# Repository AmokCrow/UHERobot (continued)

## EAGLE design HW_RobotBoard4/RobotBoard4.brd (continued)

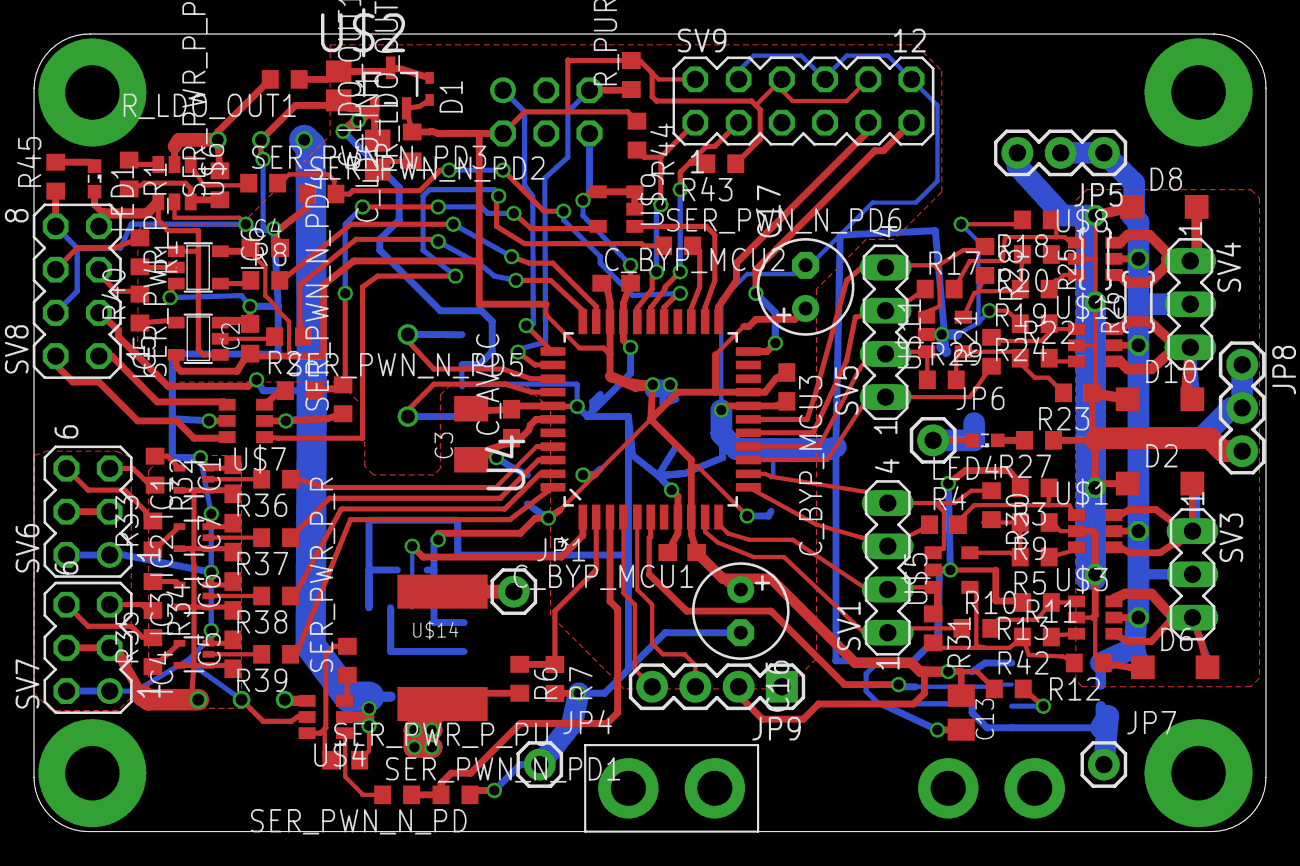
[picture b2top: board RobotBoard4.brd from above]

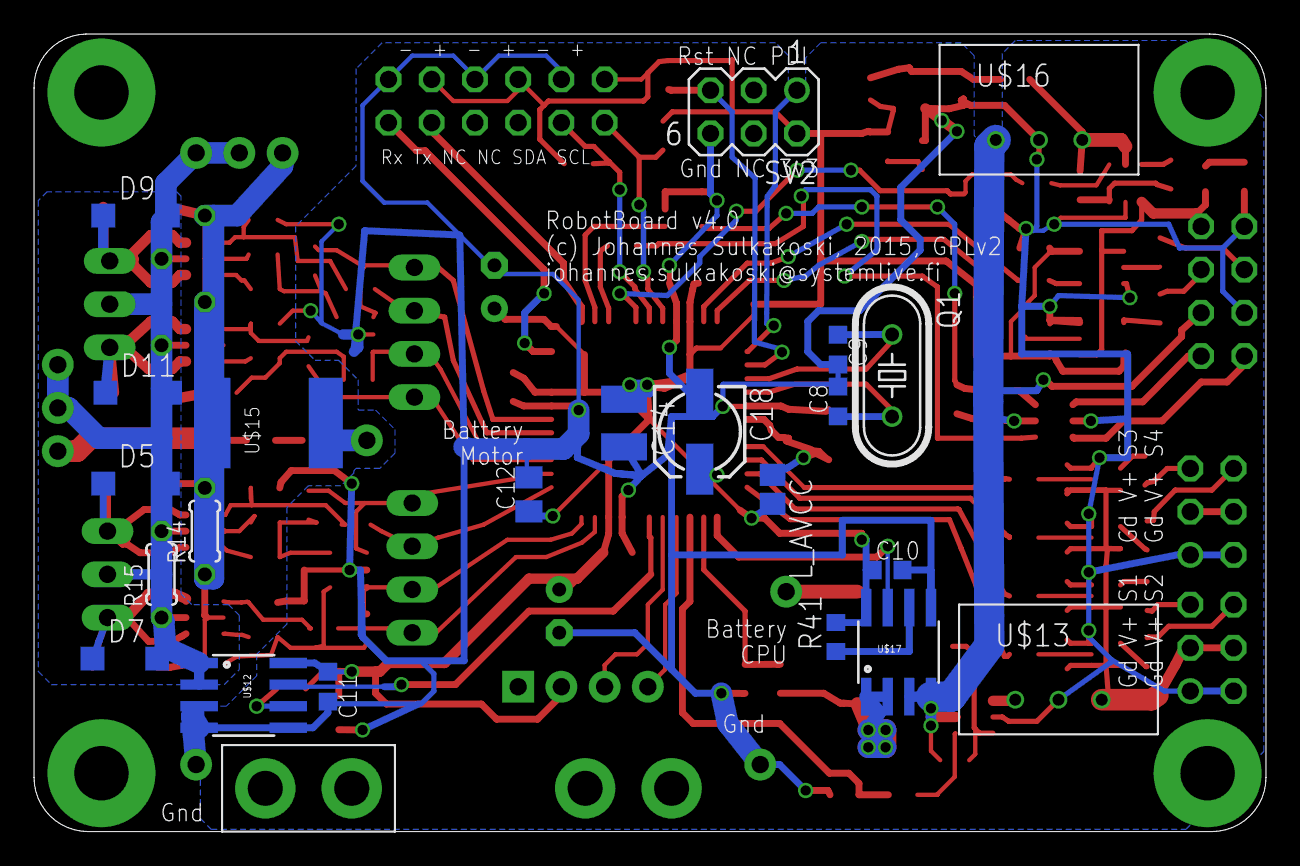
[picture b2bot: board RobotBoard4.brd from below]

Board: 4 copper layers, 72.4 x 46.9 mm, 140 parts (23 on the bottom side), 95 nets.

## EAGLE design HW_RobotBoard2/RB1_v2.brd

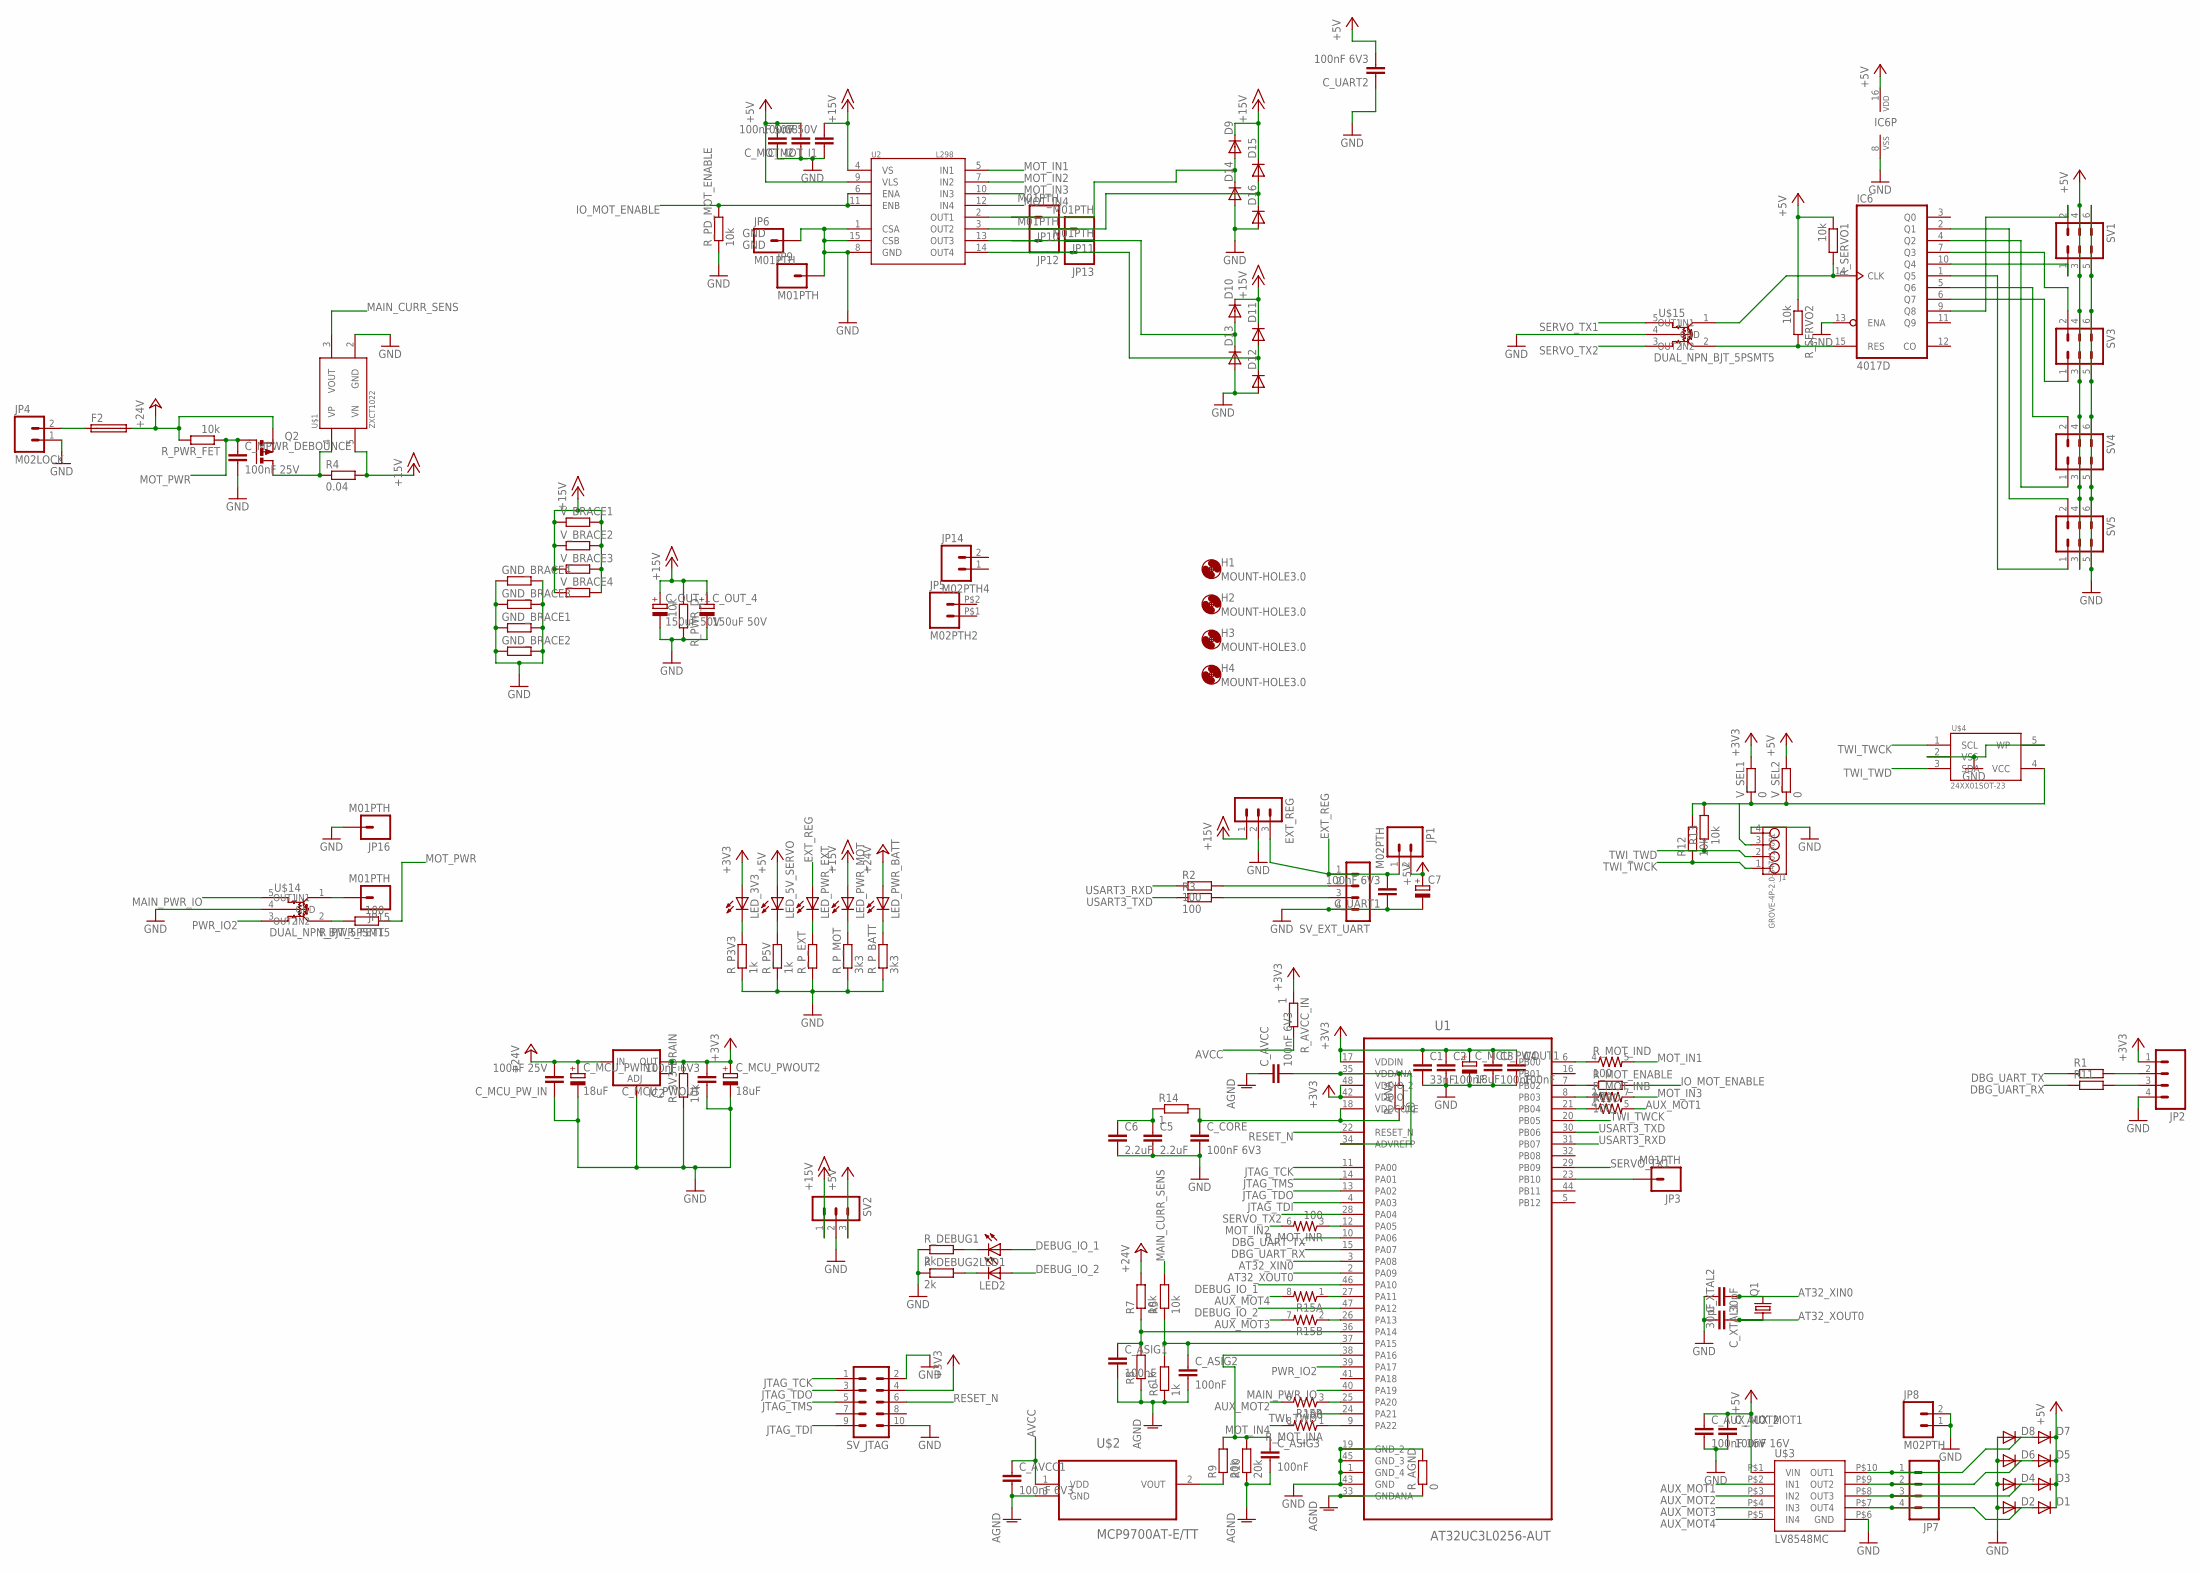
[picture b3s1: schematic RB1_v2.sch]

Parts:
C1: 33nF; C0603K
C2, C3, C4: 100nF; C0603K
C5, C6: 2.2uF; C0603K
C7: CPOL-EU153CLV-0807; 153CLV-0807
C8: C-EUC1210K; C1210K
C_ASIG1, C_ASIG2, C_ASIG3: 100nF; C0603K
C_AUX_MOT1, C_AUX_MOT2: 100nF 16V; C0603K
C_AVCC, C_AVCC1: 100nF 6V3; C0603K
C_CORE: 100nF 6V3; C0603K
C_MCU_PWIN1: 18uF; E2-5
C_MCU_PWOUT: 100nF 6V3; C0603K
C_MCU_PWOUT1, C_MCU_PWOUT2: 18uF; E2-5
C_MCU_PW_IN: 100nF 25V; C0603K
C_MOT_I1, C_MOT_I2: 100nF 50V; C0603K
C_MPWR_DEBOUNCE: 100nF 25V; C0603K
C_OUT_1, C_OUT_4: 150uF 50V; E5-10,5
C_UART1, C_UART2: 100nF 6V3; C0603K
C_XTAL1, C_XTAL2: 30pF; C0603K
D1, D2, D3, D4, D5, D6, D7, D8, D9, D10, D11, D12, D13, D14, D15, D16: DIODE-SOD123; SOD123
EXT_REG: MA03-1
F2: SHK20Q
GND_BRACE1, GND_BRACE2, GND_BRACE3, GND_BRACE4: R-EU_0204/2V; 0204V
H1, H2, H3, H4: MOUNT-HOLE3.0; 3,0
IC2: V_REG_LM1117SOT223; SOT223
IC6: 4017D; SO16
J1: GROVE-4P-2.0-3470130P1; 4P-2.0
JP1, JP8: M02PTH; 1X02
JP2, JP7: M04PTH; 1X04
JP3, JP6, JP9, JP10, JP11, JP12, JP13, JP15, JP16: M01PTH; 1X01
JP4: M02LOCK; 1X02_LOCK
JP5: M02PTH2; 1X02_BIG
JP14: M02PTH4; 1X02_XTRA_BIG
LED1, LED2: LEDCHIPLED_0603; CHIPLED_0603
LED_3V3, LED_5V_SERVO: LEDSML0603; SML0603
LED_PWR_BATT: LEDSML0603; SML0603
LED_PWR_EXT: LEDSML0603; SML0603
LED_PWR_MOT: LEDSML0603; SML0603
Q1: CRYSTALHC49S; HC49/S
Q2: P-MOSFET-SO8; SO-08
R1, R11: R-EU_R0603; R0603
R2, R3: 100; R0603
R4: 0.04; 0617/17
R5, R7, R12, R13: 10k; R0603
R6, R8: 1k; R0603
R9, R10: 20k; R0603
R14: 1; R0603
R15: RESISTOR-ARRAY0603-ARV; 0603-ARV
R_3V3_DRAIN: 10k; R0603
R_AGND: 0; R0603
R_ANA: 10; R0603
R_AVCC_IN: 1; R0603
R_DEBUG1, R_DEBUG2: 2k; R0603
R_MOT_ENABLE: 100; R0603
R_MOT_IN: 100; 0603-ARV
R_P3V3, R_P5V: 1k; R0603
R_PD_MOT_ENABLE: 10k; R0603
R_PWR_D: 10k; R0603
R_PWR_FET: 10k; R0603
R_PWR_FET1: 100; R0603
R_P_BATT: 3k3; R0603
R_P_EXT: R-EU_R0603; R0603
R_P_MOT: 3k3; R0603
R_SERVO1, R_SERVO2: 10k; R0603
SV1, SV3, SV4, SV5: MA03-2
SV2: MA03-1
SV_EXT_UART: MA04-1
SV_JTAG: MA05-2
U1: AT32UC3L0256-AUT; QFP50P900X900X120-48N
U2: L298; MULTIWATT15
U$1: ZXCT1022; SOT23-5
U$2: MCP9700AT-E/TT; SOT95P237X112-3N
U$3: LV8548MC; SOIC10
U$4: 24XX01SOT-23; SOT23-5L
U$14, U$15: DUAL_NPN_BJT_5PSMT5; SC-74A
V_BRACE1, V_BRACE2, V_BRACE3, V_BRACE4: R-EU_0204/2V; 0204V
V_SEL1, V_SEL2: 0; R0603

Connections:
+3V3: C1.1, C2.1, C3.1, C4.1, C_MCU_PWOUT.2, C_MCU_PWOUT1.+, C_MCU_PWOUT2.+, IC2.2 (OUT), IC2.4 (OUT), JP2.1, LED_3V3.A, R_3V3_DRAIN.2, R_AVCC_IN.1, SV_JTAG.4, U1.17 (VDDIN), U1.42 (VDDIO), U1.48 (VDDIO_2), V_SEL1.2
+5V: C7.+, C8.1, C_AUX_MOT1.1, C_AUX_MOT2.1, C_MOT_I2.2, C_UART2.2, D1.C, D3.C, D5.C, D7.C, IC6.16 (VDD), JP1.2, LED_5V_SERVO.A, R_SERVO1.1, R_SERVO2.1, SV1.3, SV1.4, SV2.3, SV3.3, SV3.4, SV4.3, SV4.4, SV5.3, SV5.4, U2.9 (VLS), U$3.P$1 (VIN), V_SEL2.2
+15V: C_MOT_I1.2, C_OUT_1.+, C_OUT_4.+, D9.C, D10.C, D11.C, D15.C, EXT_REG.1, LED_PWR_MOT.A, R4.2, R_PWR_D.1, SV2.1, U2.4 (VS), U$1.5 (VN), V_BRACE1.1, V_BRACE1.2, V_BRACE2.1, V_BRACE2.2, V_BRACE3.1, V_BRACE3.2, V_BRACE4.1, V_BRACE4.2
+24V: C_MCU_PWIN1.+, C_MCU_PW_IN.2, F2.2A, IC2.3 (IN), LED_PWR_BATT.A, Q2.1 (S), Q2.2 (S), Q2.3 (S), R7.2, R_PWR_FET.2
AGND: C_ASIG1.2, C_ASIG2.2, C_ASIG3.2, C_AVCC.1, C_AVCC1.2, R6.1, R8.1, R10.1, R_AGND.1, U1.33 (GNDANA), U$2.3 (GND)
AT32_XIN0: C_XTAL1.1, Q1.2, U1.3 (PA08)
AT32_XOUT0: C_XTAL2.2, Q1.1, U1.2 (PA09)
AUX_MOT1: R15.5 (2), U$3.P$2 (IN1)
AUX_MOT2: R15.6 (2), U$3.P$3 (IN2)
AUX_MOT3: R15.7 (2), U$3.P$4 (IN3)
AUX_MOT4: R15.8 (2), U$3.P$5 (IN4)
AVCC: C_AVCC1.1, R_AVCC_IN.2, U$2.1 (VDD)
BATT_VOLT_SENS: Q2.5 (D), Q2.6 (D), Q2.7 (D), Q2.8 (D), R4.1, U$1.4 (VP)
DBG_UART_RX: R11.1, U1.15 (PA07)
DBG_UART_TX: R1.1, U1.10 (PA06)
DEBUG_IO_1: LED1.A, U1.46 (PA10)
DEBUG_IO_2: LED2.A, U1.47 (PA12)
EXT_REG: C_UART1.2, EXT_REG.3, JP1.1, LED_PWR_EXT.A, SV_EXT_UART.1
GND: C1.2, C2.2, C3.2, C4.2, C5.2, C6.2, C7.-, C8.2, C_AUX_MOT1.2, C_AUX_MOT2.2, C_CORE.2, C_MCU_PWIN1.-, C_MCU_PWOUT.1, C_MCU_PWOUT1.-, C_MCU_PWOUT2.-, C_MCU_PW_IN.1, C_MOT_I1.1, C_MOT_I2.1, C_MPWR_DEBOUNCE.2, C_OUT_1.-, C_OUT_4.-, C_UART1.1, C_UART2.1, C_XTAL1.2, C_XTAL2.1, D2.A, D4.A, D6.A, D8.A, D12.A, D13.A, D14.A, D16.A, EXT_REG.2, GND_BRACE1.1, GND_BRACE1.2, GND_BRACE2.1, GND_BRACE2.2, GND_BRACE3.1, GND_BRACE3.2, GND_BRACE4.1, GND_BRACE4.2, IC2.1 (ADJ), IC6.8 (VSS), IC6.13 (ENA), J1.4, JP2.4, JP4.1, JP6.1, JP8.1, JP8.2, JP9.1, JP16.1, R_3V3_DRAIN.1, R_AGND.2, R_DEBUG1.1, R_DEBUG2.1, R_P3V3.1, R_P5V.1, R_PD_MOT_ENABLE.1, R_PWR_D.2, R_P_BATT.1, R_P_EXT.1, R_P_MOT.1, SV1.5, SV1.6, SV2.2, SV3.5, SV3.6, SV4.5, SV4.6, SV5.5, SV5.6, SV_EXT_UART.4, SV_JTAG.2, SV_JTAG.10, U1.1 (GND_4), U1.19 (GND_2), U1.43 (GND), U1.45 (GND_3), U2.1 (CSA), U2.8 (GND), U2.15 (CSB), U$1.2 (GND), U$3.P$6 (GND), U$4.2 (VSS), U$4.5 (WP), U$14.4 (GND), U$15.4 (GND)
IO_MOT_ENABLE: R_MOT_ENABLE.2, R_PD_MOT_ENABLE.2, U2.6 (ENA), U2.11 (ENB)
JTAG_TCK: SV_JTAG.1, U1.11 (PA00)
JTAG_TDI: SV_JTAG.9, U1.4 (PA03)
JTAG_TDO: SV_JTAG.3, U1.13 (PA02)
JTAG_TMS: SV_JTAG.5, U1.14 (PA01)
MAIN_CURR_SENS: R5.2, U$1.3 (VOUT)
MAIN_PWR_IO: U1.40 (PA19), U$14.5 (IN1)
MOT_IN1: R_MOT_IN.5 (2), U2.5 (IN1)
MOT_IN2: R_MOT_IN.6 (2), U2.7 (IN2)
MOT_IN3: R_MOT_IN.7 (2), U2.10 (IN3)
MOT_IN4: R_MOT_IN.8 (2), U2.12 (IN4)
MOT_O3_1: D11.A, D12.C, JP13.1, U2.14 (OUT4)
MOT_O3_2: D10.A, D13.C, JP12.1, U2.13 (OUT3)
MOT_O4_1: D15.A, D16.C, JP11.1, U2.3 (OUT2)
MOT_O4_2: D9.A, D14.C, JP10.1, U2.2 (OUT1)
MOT_PWR: C_MPWR_DEBOUNCE.1, Q2.4 (G), R_PWR_FET.1, R_PWR_FET1.1
unnamed: C_AVCC.2, R_ANA.2, U1.34 (ADVREFP), U1.35 (VDDANA)
unnamed: R9.1, U$2.2 (VOUT)
unnamed: R_MOT_IN.4 (1), U1.6 (PB00)
unnamed: R_MOT_IN.3 (1), U1.12 (PA05)
unnamed: IC6.14 (CLK), R_SERVO1.2, U$15.1 (OUT1)
unnamed: IC6.15 (RES), R_SERVO2.2, U$15.2 (OUT2)
unnamed: R_PWR_FET1.2, U$14.2 (OUT2)
unnamed: R_MOT_IN.2 (1), U1.8 (PB03)
unnamed: F2.1A, JP4.2
unnamed: J1.3, R12.2, R13.2, U$4.4 (VCC), V_SEL1.1, V_SEL2.1
unnamed: R_MOT_IN.1, U1.9 (PA22)
unnamed: LED_3V3.C, R_P3V3.2
unnamed: IC6.1 (Q5), SV5.1
unnamed: C5.1, C6.1, R14.1
unnamed: IC6.2 (Q1), SV5.2
unnamed: C_ASIG3.1, R9.2, R10.2, U1.38 (PA16)
unnamed: IC6.4 (Q2), SV4.1
unnamed: D7.A, D8.C, JP7.1, U$3.P$10 (OUT1)
unnamed: IC6.5 (Q6), SV4.2
unnamed: LED_5V_SERVO.C, R_P5V.2
unnamed: LED_PWR_EXT.C, R_P_EXT.2
unnamed: LED_PWR_MOT.C, R_P_MOT.2
unnamed: IC6.6 (Q7), SV3.1
unnamed: IC6.7 (Q3), SV3.2
unnamed: C_ASIG1.1, R7.1, R8.2, U1.36 (PA14)
unnamed: C_ASIG2.1, R5.1, R6.2, U1.37 (PA15)
unnamed: IC6.9 (Q8), SV1.2
unnamed: LED_PWR_BATT.C, R_P_BATT.2
unnamed: D5.A, D6.C, JP7.2, U$3.P$9 (OUT2)
unnamed: D3.A, D4.C, JP7.3, U$3.P$8 (OUT3)
unnamed: D1.A, D2.C, JP7.4, U$3.P$7 (OUT4)
unnamed: IC6.10 (Q4), SV1.1
unnamed: JP2.3, R11.2
unnamed: JP2.2, R1.2
unnamed: R_MOT_ENABLE.1, U1.7 (PB02)
unnamed: JP3.1, U1.23 (PB10)
unnamed: R15.4 (1), U1.21 (PB04)
unnamed: R15.3 (1), U1.25 (PA20)
unnamed: R15.2 (1), U1.26 (PA13)
unnamed: R15.1, U1.27 (PA11)
unnamed: JP15.1, U$14.1 (OUT1)
unnamed: LED1.C, R_DEBUG1.2
unnamed: LED2.C, R_DEBUG2.2
unnamed: C_CORE.1, R14.2, R_ANA.1, U1.18 (VDDCORE)
PWR_IO2: U1.39 (PA17), U$14.3 (IN2)
RESET_N: SV_JTAG.6, U1.22 (RESET_N)
SERVO_TX1: U1.29 (PB09), U$15.5 (IN1)
SERVO_TX2: U1.28 (PA04), U$15.3 (IN2)
TWI_TWCK: J1.1, R12.1, U1.20 (PB05), U$4.1 (SCL)
TWI_TWD: J1.2, R13.1, U1.24 (PA21), U$4.3 (SDA)
USART3_RXD: R2.1, U1.31 (PB07)
USART3_RXD_2: R2.2, SV_EXT_UART.2
USART3_TXD: R3.1, U1.30 (PB06)
USART3_TXD_2: R3.2, SV_EXT_UART.3

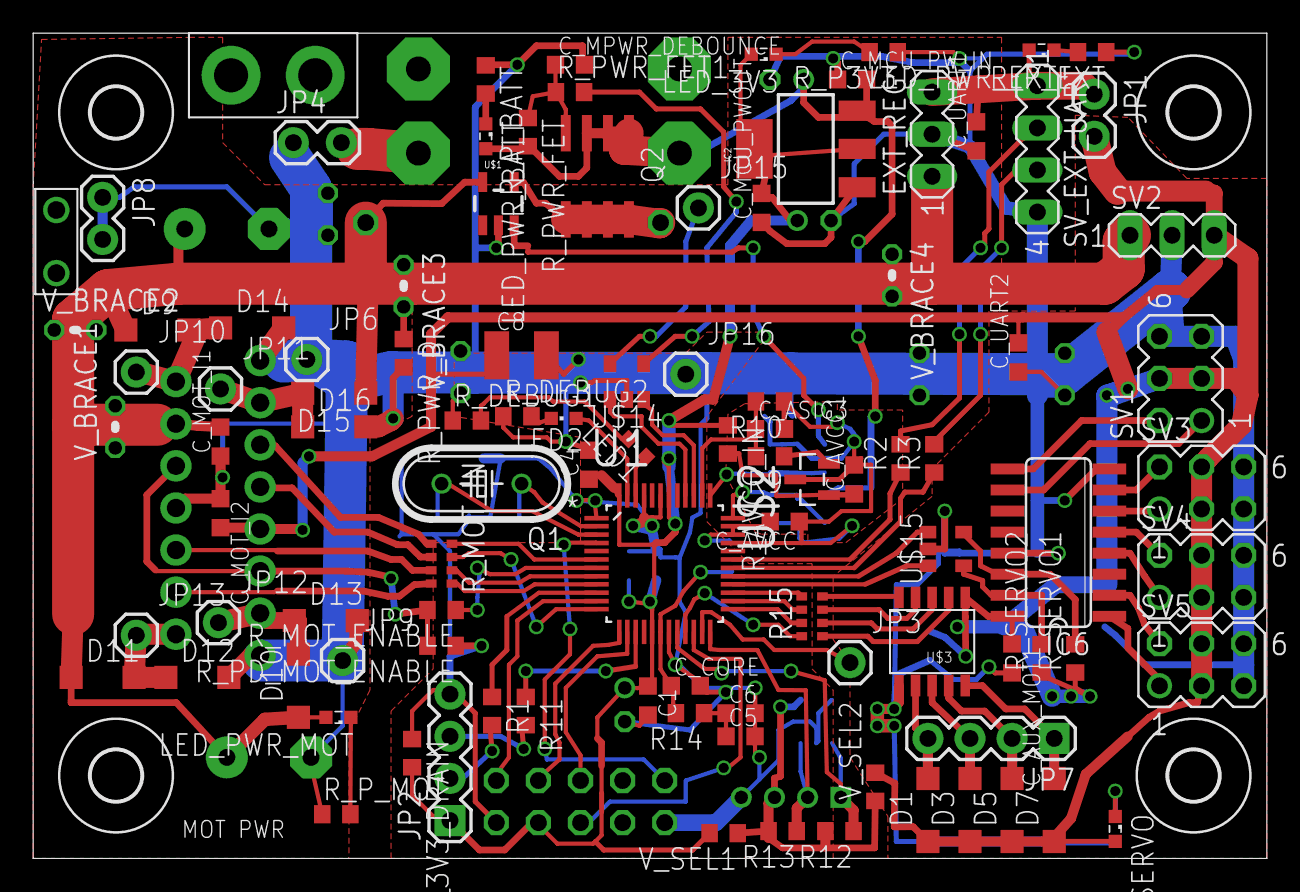
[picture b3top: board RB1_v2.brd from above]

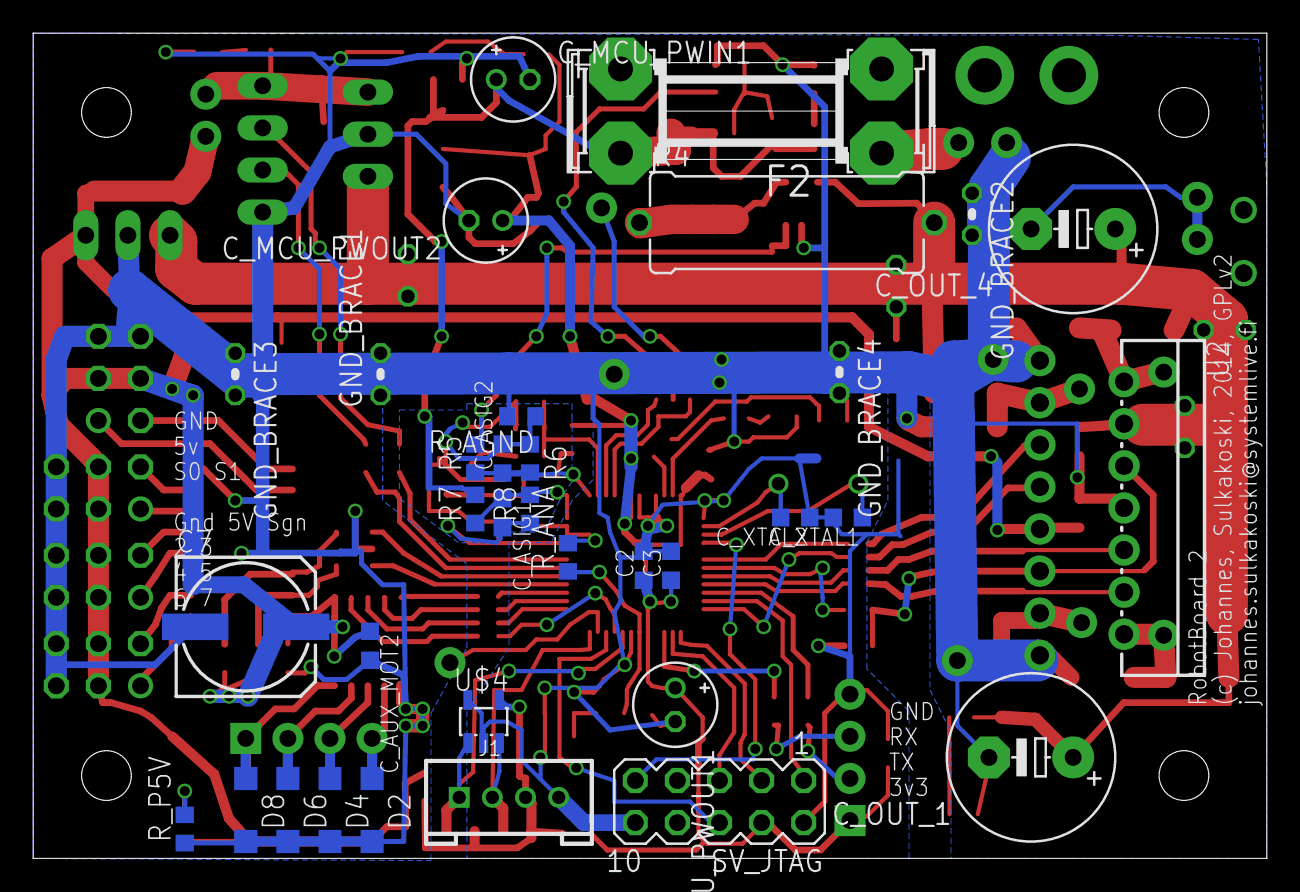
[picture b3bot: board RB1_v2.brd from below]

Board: 4 copper layers, 74.4 x 49.8 mm, 139 parts (34 on the bottom side), 89 nets.

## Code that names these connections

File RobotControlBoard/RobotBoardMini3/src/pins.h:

/*
 * pins.h
 *
 * Created: 16.1.2016 20:25:29
 *  Author: crow
 */ 


#ifndef PINS_H_
#define PINS_H_

#include <avr32/uc3l032.h>

#define PIN_5V_OUT      AVR32_PIN_PB02
#define PIN_12V_OUT     AVR32_PIN_PB03
#define PIN_5V_PD_OUT   AVR32_PIN_PA22
#define PIN_12V_PD_OUT  AVR32_PIN_PA06
#define PIN_STATUS_LED  AVR32_PIN_PA20

#if 1
#define PIN_ENA_MOT_PWR AVR32_PIN_PA11
#else
#define PIN_ENA_MOT_PWR AVR32_PIN_PA14
#endif

#define PIN_ENA_FAN_PWR AVR32_PIN_PA04
#define PIN_AUX_IO1     AVR32_PIN_PA13
#define PIN_AUX_OUT3     AVR32_PIN_PA00
#define PIN_AUX_IO4     AVR32_PIN_PB11

#define PIN_MOT_1A      AVR32_PIN_PA19
#define PIN_MOT_1B      AVR32_PIN_PA18

#define PIN_MOT_2A      AVR32_PIN_PA10
#define PIN_MOT_2B      AVR32_PIN_PA12

#define PIN_UART_TX     AVR32_PIN_PA02
#define PIN_UART_RX     AVR32_PIN_PA07

// Pins are already configured as 5V pull-down at startup.
#define PIN_SDA_5V      AVR32_PIN_PA21
#define PIN_SCL_5V      AVR32_PIN_PB05

#define PIN_SDA         AVR32_PIN_PA17
#define PIN_SCL         AVR32_PIN_PA05

#define PIN_ADC_TEMP            AVR32_PIN_PB08
#define PIN_ADC_MAIN_BATT_VOLT  AVR32_PIN_PB07
#define PIN_ADC_MAIN_BATT_CURR  AVR32_PIN_PB06
#define PIN_ADC_MOT_BATT_VOLT   AVR32_PIN_PA16
#define PIN_ADC_MOT_CURR        AVR32_PIN_PA15

#define PIN_INPUT_FAN_SPD       AVR32_PIN_PB09


#endif /* PINS_H_ */

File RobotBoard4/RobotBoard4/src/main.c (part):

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#include "ServoTimer.h"
#include "MotorFunctions.h"

#define PIN_DEBUG_TX IOPORT_CREATE_PIN(PORTD, 3)
#define PIN_DEBUG_RX IOPORT_CREATE_PIN(PORTD, 2)

#define PIN_SERVO1 IOPORT_CREATE_PIN(PORTD, 1)
#define PIN_SERVO2 IOPORT_CREATE_PIN(PORTD, 0)

#define PIN_PWR_LED  IOPORT_CREATE_PIN(PORTD, 7)
#define PIN_PWR_CPU  IOPORT_CREATE_PIN(PORTD, 6)
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ServoTimer_Servo_t servos[2] =
{
    {
        PIN_SERVO1,
        100
    },
    {
        PIN_SERVO2,
        100
    }
};
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ServoTimer_Servo_t servos[2] =
{
    {
        PIN_DEBUG_TX,
        100
    },
    {
        PIN_DEBUG_RX,
        100
    }
};
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        }
        
        commandsReceived = 1;
        ioport_set_pin_level(PIN_SERVO1, true);
        ioport_set_pin_level(PIN_SERVO2, true);
        
        memcpy(inCommBuff, cmdBuff.cmdParams, cmdBuff.cmdParamsLength);
        inCommLength = cmdBuff.cmdParamsLength;
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    uOpts.paritytype = USART_PMODE_DISABLED_gc;
    uOpts.stopbits = false;
    
    //ioport_set_pin_mode(PIN_DEBUG_TX, IOPORT_MODE_TOTEM);
    //ioport_set_pin_dir(PIN_DEBUG_TX, IOPORT_DIR_OUTPUT);
    
    ioport_set_pin_mode(PIN_PWR_CPU, IOPORT_MODE_TOTEM);
    ioport_set_pin_level(PIN_PWR_CPU, true);
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        motor_set_speed(0, 0);
        motor_set_speed(0, 1);
        
        ioport_set_pin_level(PIN_SERVO1, false);
        ioport_set_pin_level(PIN_SERVO2, false);
    }
    
    commandsReceived = 0;
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    
    start_motor_clock();
    
    ioport_set_pin_dir(PIN_SERVO1, IOPORT_DIR_OUTPUT);
    ioport_set_pin_dir(PIN_SERVO2, IOPORT_DIR_OUTPUT);
    
    configure_uarts();
    
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
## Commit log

2014-02-01 Initial commit with README
2014-02-01 Added initial version of RobotControlBoard
2014-02-01 Initial RobotControlDaemon
2014-02-01 Initial RobotControlDaemon 2
2014-02-04 Started documentation
2014-02-06 More documentation
2014-02-08 MCreated messageparser class and took in QTCreator IDE for project
2014-02-10 More work on the BASE16 transceiver class
2014-02-10 Forgot a file
2014-02-10 Only encoding and sending missing from UART side. And threading..
2014-02-14 Added some read functionality.
2014-02-14 Started the Base16Message class. Made first version of header for it and started on the cpp side.
2014-02-15 Finished Base16Message class
2014-02-15 Almost finished rewrite of MessageParser class
2014-02-20 Base16Message and serial communication compile.
2014-02-22 Started linux-pipe reader
2014-03-27 Added fcgi test meterial to project
2014-04-07 Updated plans. See README
2014-04-18 Functional FastCGI server internals in fcgi_test main.cpp
2014-04-19 Further work on the FCGI server part. Mostly complete
2014-04-19 Debugged serial sending
2014-04-20 Serial comms fully debugged. Or at least to the point that data goes back and forth
2014-04-20 Connected the web parts to ControlLogic
2014-04-20 Web interfacing works
2014-04-21 Just before attempting to cross-compile qith qmake
2014-04-26 Just in case
2014-04-26 Removed fcgi_test
2014-04-26 Minor touchup and documentation weeding
2014-04-26 Driving should now work
2014-04-30 Changed FcgiServer to use pthread library, due to a bug in Raspbian c++11 libraries.
2014-05-01 Changed serial communication to use pthreads too.
2014-05-03 Motor control via web works. Needs cleaning though.
2014-07-28 Added new board code
2014-09-04 New deployment scripts for daemon
2014-09-06 Added beginnings of debug log. Further deployment script development.
2014-09-06 Finished logging class
2014-09-07 Changed serial comms format to tag-data.
2014-09-10 Further towards a tag-data format
2014-09-13 Finished server interface change
2014-09-21 Futher work on daemon.
2014-10-11 Defined all the pins and functions of RobotControlBoard2.
2014-10-13 Servo4017 mostly finished. Main changed from C to CPP file extension.
2014-11-07 Added Servo4017 final and MotorControl initial.
2014-11-27 Finished code to get both motors moving. Plus debug commands.
2014-11-28 Finished debug stats printing with selfmade functions.
2014-11-29 Changed server to main thread communication method
2014-12-03 A change in logic
2014-12-09 Some further work.
2014-12-13 Mostly finished daemon.
2014-12-17 Fixed a JSON bug.
2014-12-19 Debugged communication board to daemon.
2014-12-19 Debugged the other end of the board to daemon communications.
2014-12-21 Minor modification to deployment scripts.
2015-03-14 Added attributes to keep Eagle files binary-intact. Eagle tends to get cranky when someone changes the line-endings.
2015-03-14 Added hardware files.
2015-03-21 Changed control UART to correct port.
2015-03-21 Further work on the installation scripts
2015-03-21 Fixed a few bugs in install scripts
2015-06-13 Added RobotBoard4 files.
2015-06-20 Board control SW work.
2015-06-27 Got the new board to give stats to Daemon and Fcgi.
2015-06-28 Robot moves successfully.
2015-07-04 Tightened the control loop.
2015-07-04 Board changes to get robot to function.
2015-07-05 Added servo code to robot board.
2015-07-06 Added camera and shutdown scripts.
2015-07-06 Added an ignore file.
2015-07-07 Copied RobotBoard4 schematic and layout from schemas repo for publishing.
2015-07-18 Small refinements of the HTML interface and camera script.
2015-08-28 Moved pin mappings and ADC of RobotBoard4 to the new board revision 4.2 .
2015-08-29 Redressed the protocol used to report adc results from RobotBoard4.2
2015-09-22 Fix in index.html . Redid the ADC readings handling to be more uniform.
2015-11-14 Added mjpeg-streamer to the run_camera script.
2015-12-19 Minor fixes and adaptations.
2016-01-23 Added RobotBoardMini3 initial version.
2016-02-04 Added initial CMakeLists. Updated README.
2016-02-06 Finished CMakeLists. Will now compile for Arietta G25.
2016-02-06 Enabled power to motors and CPU in the board control code.
2016-02-07 Motors now move correctly. Whenever the rx interrupts get processed soon enough anyways.
2016-02-13 Added analogs scaling to MCU. Now the Linux SW only does data propagation. Less specific to this one board, etc..
2016-02-14 Cleaned up the message interpreter in the Daemon.
2016-02-20 Minor touchups to MCU SW.
2016-02-22 Updated README.
2016-02-22 Removed obsolete folders.
2016-02-22 Copied over new HW files.
